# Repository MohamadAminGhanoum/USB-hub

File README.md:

# USB-hub
I decided to build a usb-hub that has 1 primary usb-c and 3 other usb-a ports. i want to use this to expand the usb sockets on my computer and be able to connect more devices. Im also planning to use this to connect it to my phone so that i can connect my mouse to it, and even my keyboard if i want.

## Schematics & PCB:

## 3d model of pcb:

## BOM

|FIELD1                    |Price|Amout|Link                                                                                                                                                                                                                                          |
|--------------------------|-----|-----|----------------------------------------------------------------------------------------------------------------------------------------------------------------------------------------------------------------------------------------------|
|10uF capacitor            |0.88 |20   |https://www.lcsc.com/product-detail/C92487.html?spm=wm.gwc.xh.0.tp___wm.sxq.ssl.gwc&lcsc_vid=FAAKVgBSElEKVVRRQlVbVAdfRlFXUlFfRwBeAgcCT1kxVlNeRVVXVl1WQFdeVzsOAxUeFF5JWBYZEEoKFBINSQcJGk4eFQsCAgIaSgADAwAHC0slRlhZV1ZIHxUDCw%3D%3D             |
|onsemi NSR0320MW2T1G diode|1.11 |10   |https://www.lcsc.com/product-detail/C48192.html?spm=wm.gwc.xh.1.tp___wm.sxq.ssl.gwc&lcsc_vid=FAAKVgBSElEKVVRRQlVbVAdfRlFXUlFfRwBeAgcCT1kxVlNeRVVXVl1WQFdeVzsOAxUeFF5JWBYZEEoKFBINSQcJGk4eFQsCAgIaSgADAwAHC0slRlhZV1ZIHxUDCw%3D%3D             |
|USB-A Port                |0.46 |10   |https://www.lcsc.com/product-detail/C46407.html?spm=wm.gwc.xh.2.tp___wm.sxq.ssl.gwc&lcsc_vid=FAAKVgBSElEKVVRRQlVbVAdfRlFXUlFfRwBeAgcCT1kxVlNeRVVXVl1WQFdeVzsOAxUeFF5JWBYZEEoKFBINSQcJGk4eFQsCAgIaSgADAwAHC0slRlhZV1ZIHxUDCw%3D%3D             |
|USB-C port                |0    |1    |self sourced                                                                                                                                                                                                                                  |
|220 ohm resistor          |0    |1    |self sourced                                                                                                                                                                                                                                  |
|CoreChips SL2.1A          |1.35 |5    |https://www.lcsc.com/product-detail/C6798314.html?s_z=n_q_CoreChips%2520SL2.1A&spm=wm.fly.bg.0.stp&lcsc_vid=FAAKVgBSElEKVVRRQlVbVAdfRlFXUlFfRwBeAgcCT1kxVlNeRVRZVF1UQVFZUDsOAxUeFF5JWBYZEEoKFBINSQcJGk4eFQsCAgIaSgADAwAHC0slRlhcX11VWQkaCgg%3D|
|PCB          |4.5    |5    |JLCPCB                                                                                                                                                                                                                                  |
|TOTAL cost with shipping:          |21.5 usd    |    |

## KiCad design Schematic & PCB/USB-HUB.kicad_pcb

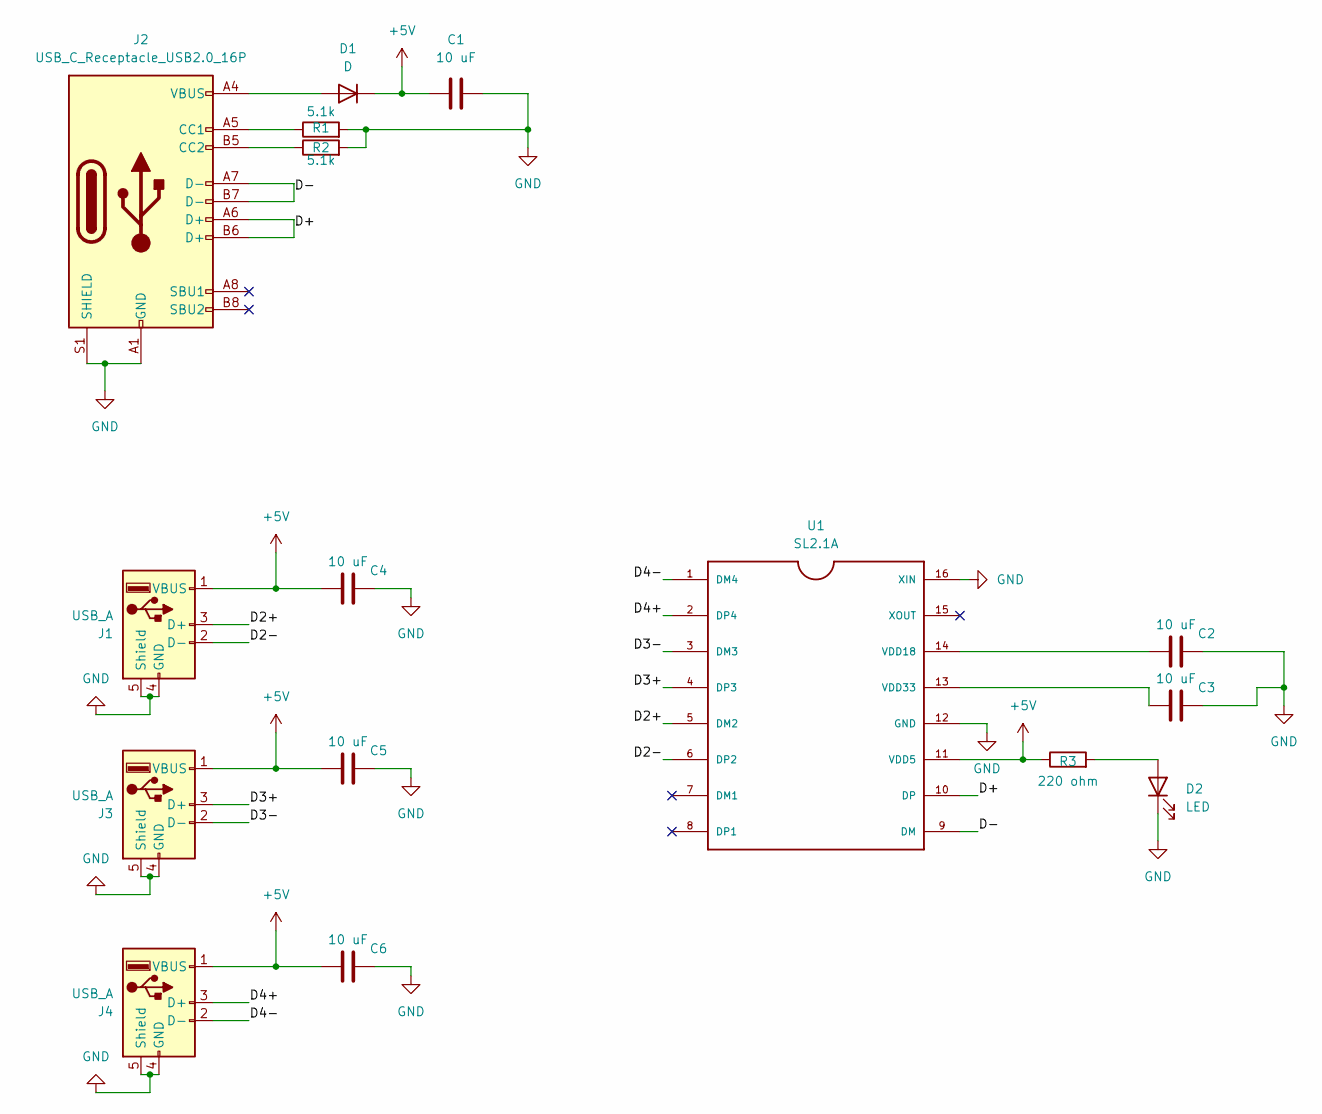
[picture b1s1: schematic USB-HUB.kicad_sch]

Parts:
C1, C2, C3, C4, C5, C6: 10 uF; C_0603_1608Metric
D1: D; D_SOD-323
D2: LED; LED_0603_1608Metric
J1, J3, J4: USB_A; USB_A_Molex_67643_Horizontal
J2: USB_C_Receptacle_USB2.0_16P; USB_C_Receptacle_XKB_U262-16XN-4BVC11
R1, R2: 5.1k; R_0603_1608Metric
R3: 220 ohm; R_0603_1608Metric
U1: SL2.1A; SO16

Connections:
+5V: C1.1, C4.1, C5.1, C6.1, D1.1 (K), J1.1 (VBUS), J3.1 (VBUS), J4.1 (VBUS), R3.1, U1.11 (VDD5)
/D2+: J1.3 (D+), U1.5 (DM2)
/D2-: J1.2 (D-), U1.6 (DP2)
/D3+: J3.3 (D+), U1.4 (DP3)
/D3-: J3.2 (D-), U1.3 (DM3)
/D4+: J4.3 (D+), U1.2 (DP4)
/D4-: J4.2 (D-), U1.1 (DM4)
/D+: J2.A6 (D+), J2.B6 (D+), U1.10 (DP)
/D-: J2.A7 (D-), J2.B7 (D-), U1.9 (DM)
GND: C1.2, C2.2, C3.2, C4.2, C5.2, C6.2, D2.1 (K), J1.4 (GND), J1.5 (Shield), J2.A1 (GND), J2.A12 (GND), J2.B1 (GND), J2.B12 (GND), J2.S1 (SHIELD), J3.4 (GND), J3.5 (Shield), J4.4 (GND), J4.5 (Shield), R1.2, R2.2, U1.12 (GND), U1.16 (XIN)
unnamed: D1.2 (A), J2.A4 (VBUS), J2.A9 (VBUS), J2.B4 (VBUS), J2.B9 (VBUS)
unnamed: D2.2 (A), R3.2
unnamed: J2.A5 (CC1), R1.1
unnamed: J2.B5 (CC2), R2.1
unnamed: C2.1, U1.14 (VDD18)
unnamed: C3.1, U1.13 (VDD33)

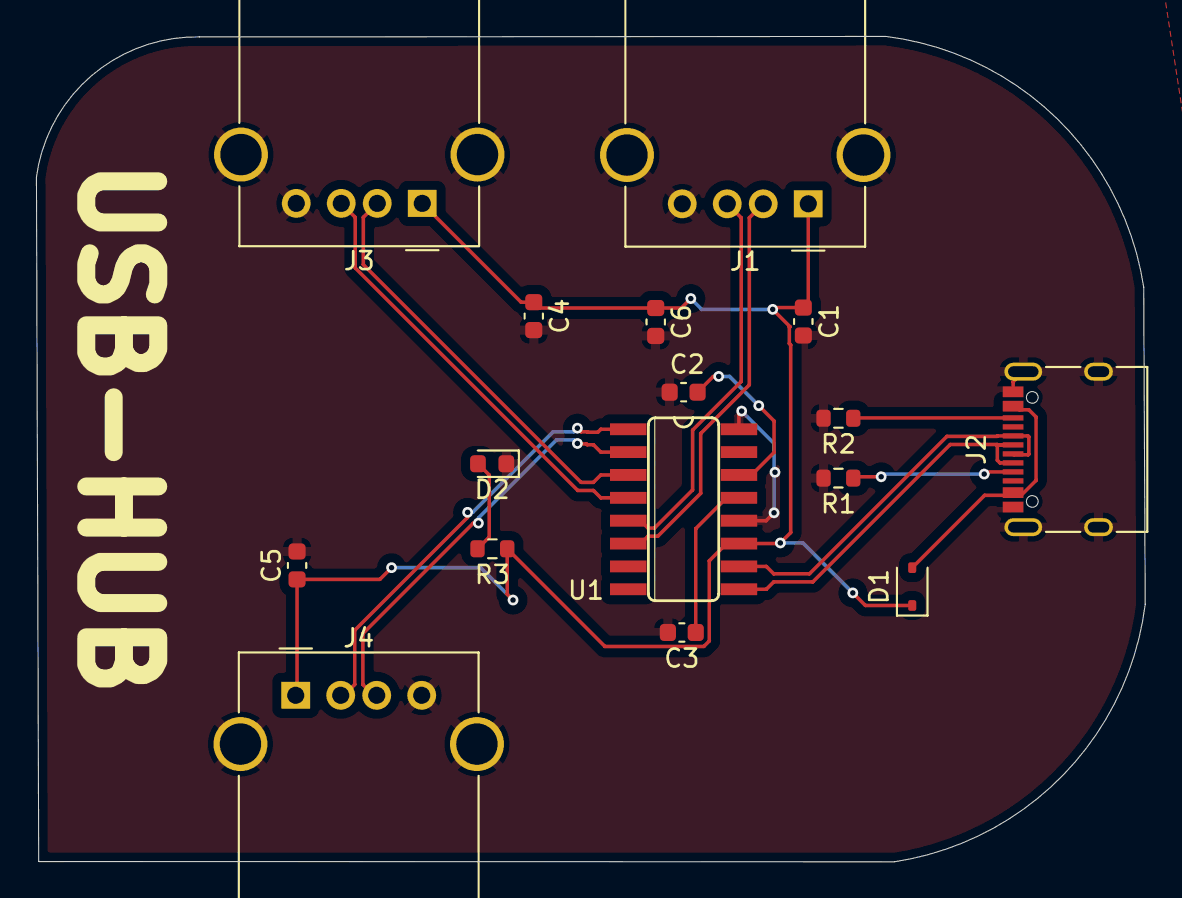
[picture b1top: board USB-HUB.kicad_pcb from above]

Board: 2 copper layers, 61.6 x 45.9 mm, 16 parts (0 on the bottom side), 16 nets.

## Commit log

2026-06-27 Adjust image size in README for PCB model
    Updated image dimensions for PCB model screenshot.
2026-06-27 Rename Screenshot 2026-06-27 at 17.10.31.png to assets/Screenshot 2026-06-27 at 17.10.31.png
2026-06-27 Rename USB-HUB.kicad_pro to Schematic & PCB/USB-HUB.kicad_pro
2026-06-27 Update README to include BOM section
    Added BOM section with component details and links.
2026-06-27 Update README with detailed project description
    Expanded description of the USB hub project, detailing its features and intended use.
2026-06-27 Add PCB entry to components list in README
2026-06-27 Update total cost in README
    Updated total cost with shipping in the README.
